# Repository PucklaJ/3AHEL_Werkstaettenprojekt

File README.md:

# 3AHEL_Werkstaettenprojekt
Hier findet man alle Dateien für unser Werktättenprojekt

Jahrgang: 2016/17
Personen:
	- Karayanov Vitaliy
	- Mujic Haris
	- Pucher Jonas

Arbeitszeit: 11x8 Schulstunden

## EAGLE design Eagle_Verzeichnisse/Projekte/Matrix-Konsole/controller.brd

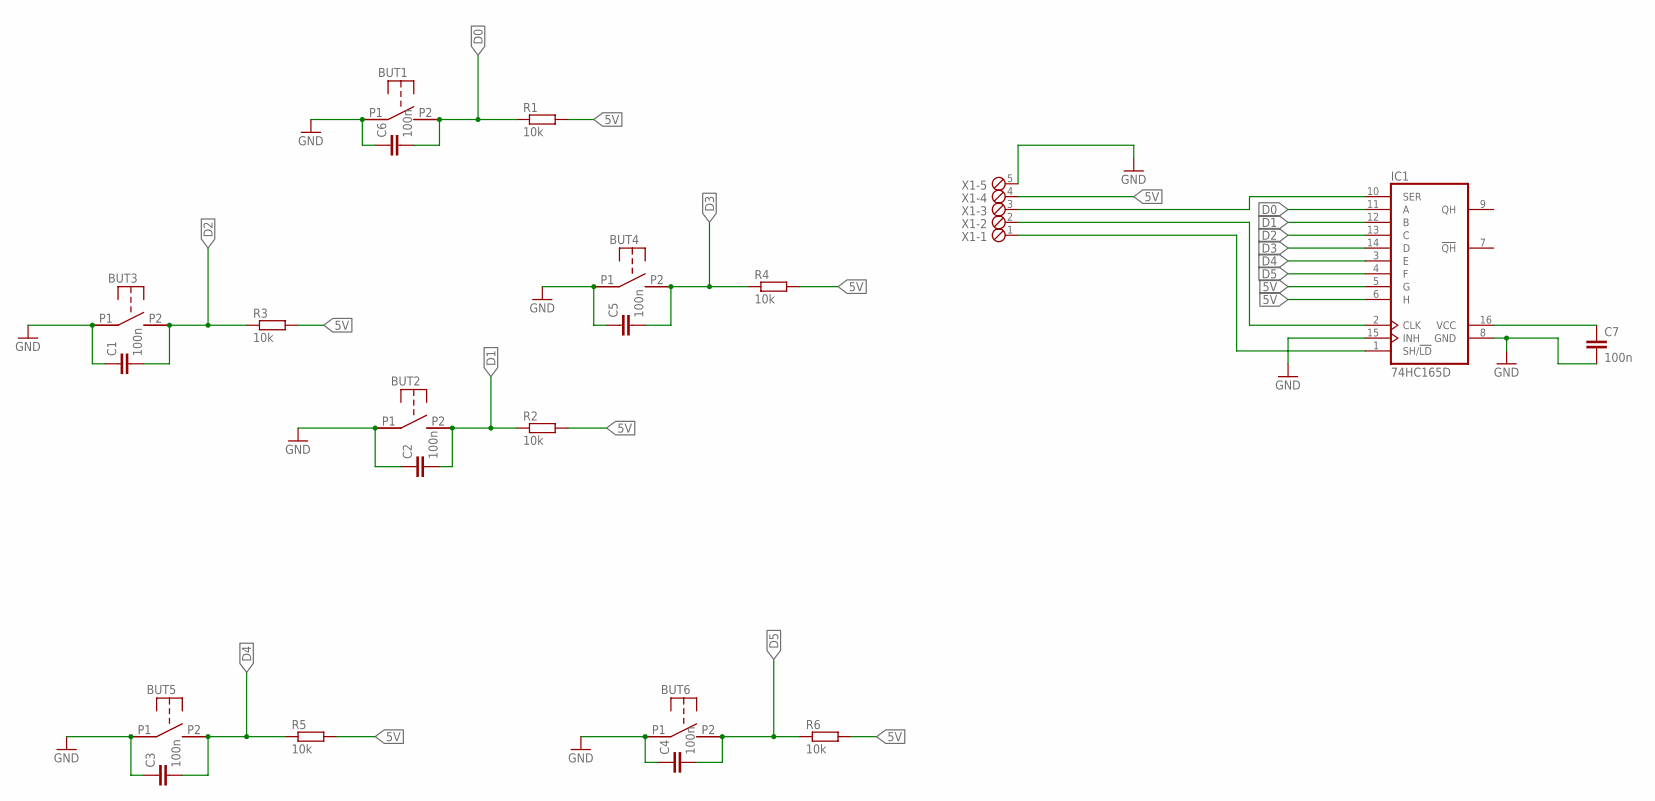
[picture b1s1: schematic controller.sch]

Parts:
BUT1, BUT2, BUT3, BUT4, BUT5, BUT6: BUTTON_DEV; BUTTON_PACK
C1, C2, C3, C4, C5, C6, C7: 100n; C0805
IC1: 74HC165D; SO16
R1, R2, R3, R4, R5, R6: 10k; M3516
X1: MPT5; 5POL254

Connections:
5V: C7.1, IC1.5 (G), IC1.6 (H), IC1.16 (VCC), R1.2, R2.2, R3.2, R4.2, R5.2, R6.2, X1.4
D0: BUT1.P2, BUT1.P2' (P2), C6.2, IC1.11 (A), R1.1
D1: BUT2.P2, BUT2.P2' (P2), C2.2, IC1.12 (B), R2.1
D2: BUT3.P2, BUT3.P2' (P2), C1.2, IC1.13 (C), R3.1
D3: BUT4.P2, BUT4.P2' (P2), C5.2, IC1.14 (D), R4.1
D4: BUT5.P2, BUT5.P2' (P2), C3.2, IC1.3 (E), R5.1
D5: BUT6.P2, BUT6.P2' (P2), C4.2, IC1.4 (F), R6.1
GND: BUT1.P1, BUT1.P1' (P1), BUT2.P1, BUT2.P1' (P1), BUT3.P1, BUT3.P1' (P1), BUT5.P1, BUT5.P1' (P1), BUT6.P1, BUT6.P1' (P1), C1.1, C2.1, C3.1, C4.1, C6.1, C7.2, IC1.8 (GND), IC1.15 (INH), X1.5
N3: BUT4.P1, BUT4.P1' (P1), C5.1
unnamed: IC1.1 (SH/!LD), X1.1
unnamed: IC1.2 (CLK), X1.2
unnamed: IC1.10 (SER), X1.3

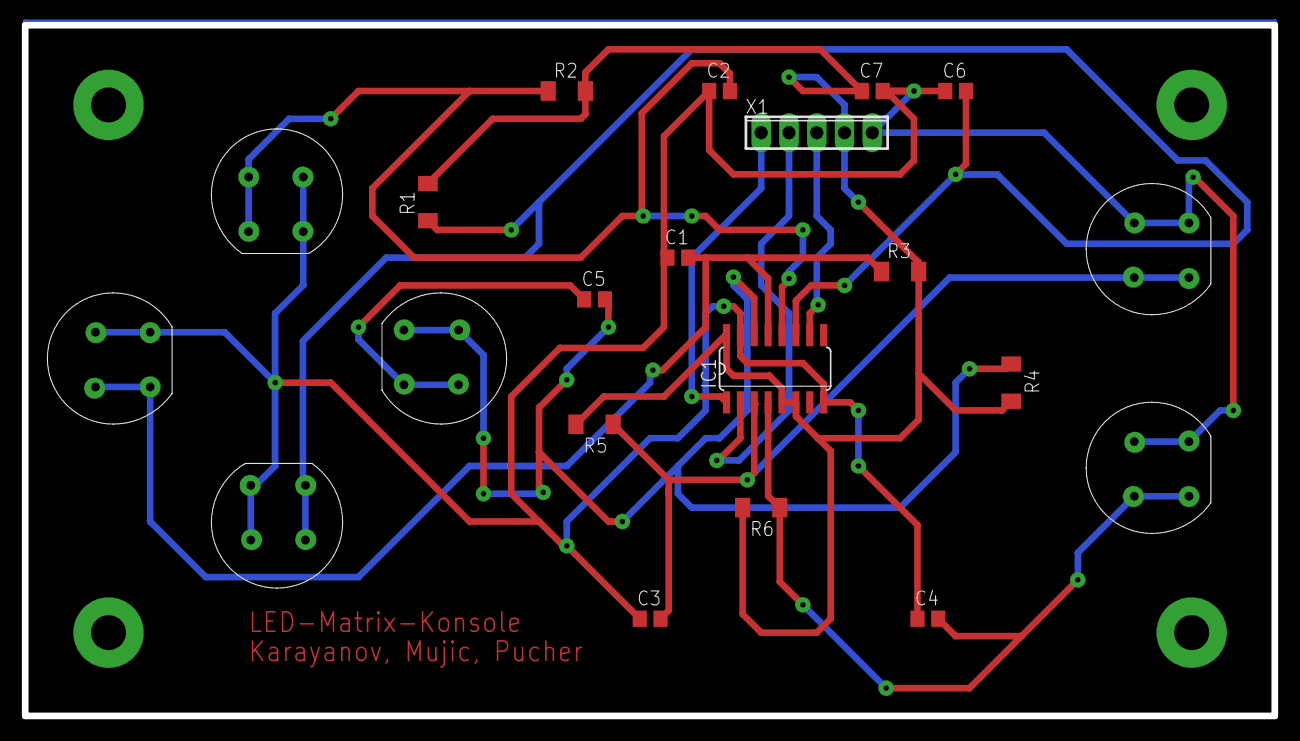
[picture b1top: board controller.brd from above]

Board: 2 copper layers, 114.3 x 63.2 mm, 21 parts (0 on the bottom side), 12 nets.

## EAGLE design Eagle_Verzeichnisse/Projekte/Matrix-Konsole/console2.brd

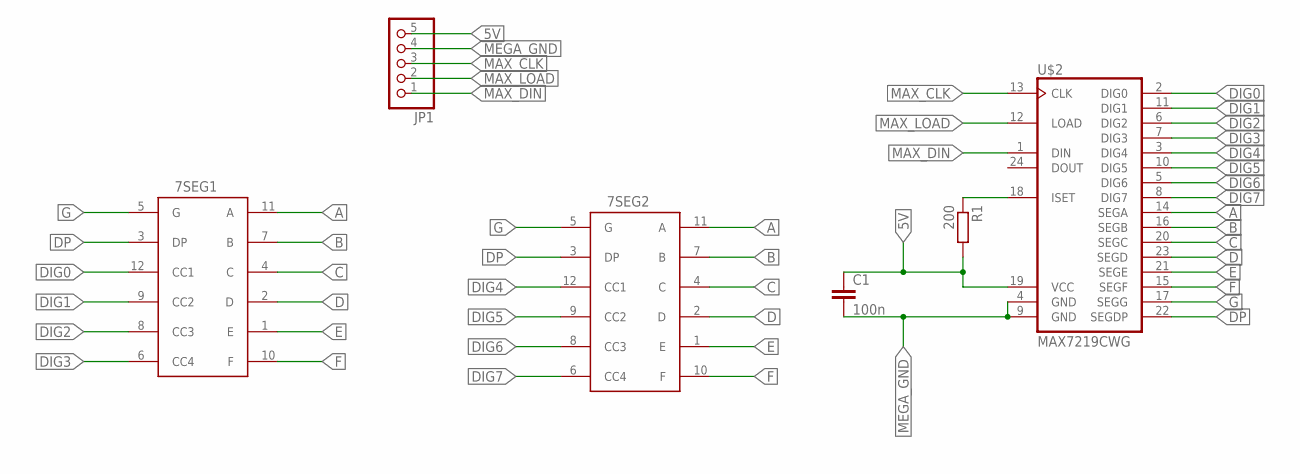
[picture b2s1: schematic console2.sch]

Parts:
7SEG1, 7SEG2: 7SEG_DEV; 7SEG_PACK
C1: 100n; C0805
JP1: PINHD-1X5; 1X05
R1: 200; M3516
U$2: MAX7219CWG; SO24L

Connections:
5V: C1.1, JP1.5, R1.2, U$2.19 (VCC)
A: 7SEG1.11 (A), 7SEG2.11 (A), U$2.14 (SEGA)
B: 7SEG1.7 (B), 7SEG2.7 (B), U$2.16 (SEGB)
C: 7SEG1.4 (C), 7SEG2.4 (C), U$2.20 (SEGC)
D: 7SEG1.2 (D), 7SEG2.2 (D), U$2.23 (SEGD)
DIG0: 7SEG1.12 (CC1), U$2.2 (DIG0)
DIG1: 7SEG1.9 (CC2), U$2.11 (DIG1)
DIG2: 7SEG1.8 (CC3), U$2.6 (DIG2)
DIG3: 7SEG1.6 (CC4), U$2.7 (DIG3)
DIG4: 7SEG2.12 (CC1), U$2.3 (DIG4)
DIG5: 7SEG2.9 (CC2), U$2.10 (DIG5)
DIG6: 7SEG2.8 (CC3), U$2.5 (DIG6)
DIG7: 7SEG2.6 (CC4), U$2.8 (DIG7)
DP: 7SEG1.3 (DP), 7SEG2.3 (DP), U$2.22 (SEGDP)
E: 7SEG1.1 (E), 7SEG2.1 (E), U$2.21 (SEGE)
F: 7SEG1.10 (F), 7SEG2.10 (F), U$2.15 (SEGF)
G: 7SEG1.5 (G), 7SEG2.5 (G), U$2.17 (SEGG)
MAX_CLK: JP1.3, U$2.13 (CLK)
MAX_DIN: JP1.1, U$2.1 (DIN)
MAX_ISET: R1.1, U$2.18 (ISET)
MAX_LOAD: JP1.2, U$2.12 (LOAD)
MEGA_GND: C1.2, JP1.4, U$2.4 (GND), U$2.9 (GND)

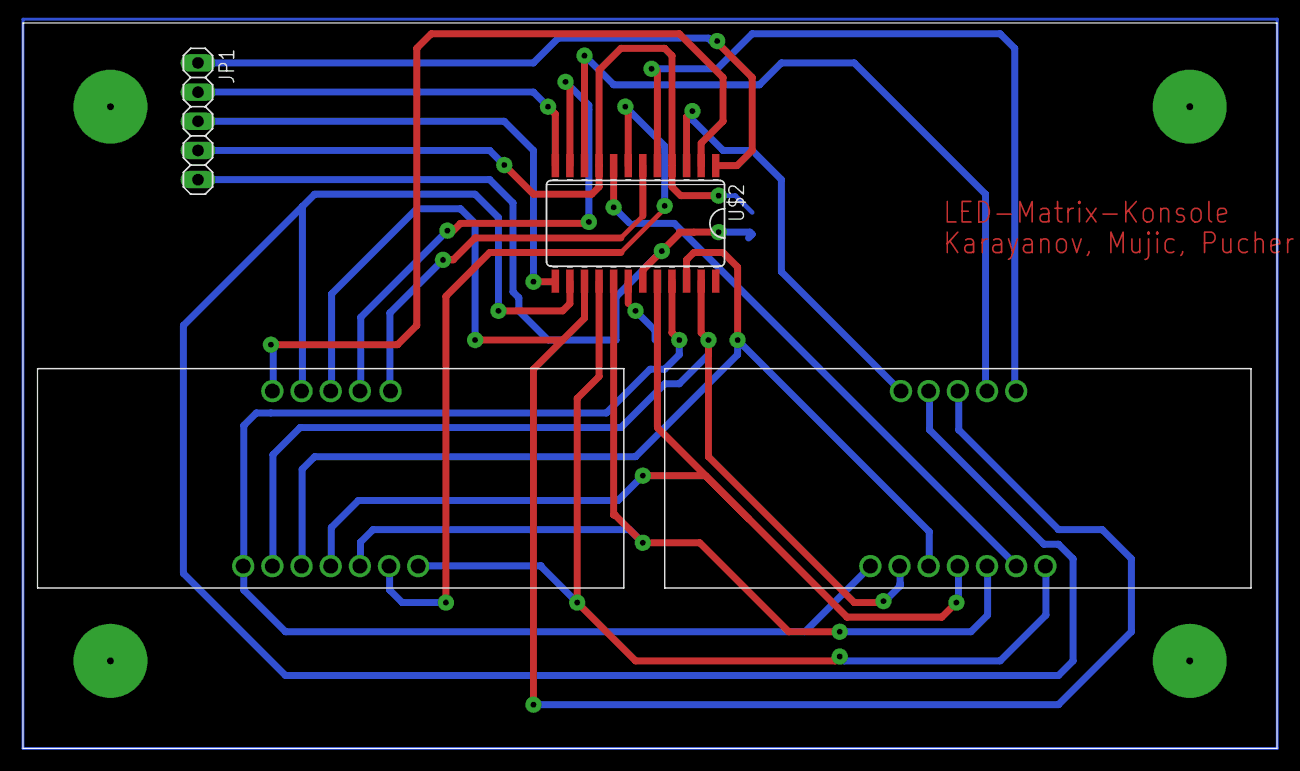
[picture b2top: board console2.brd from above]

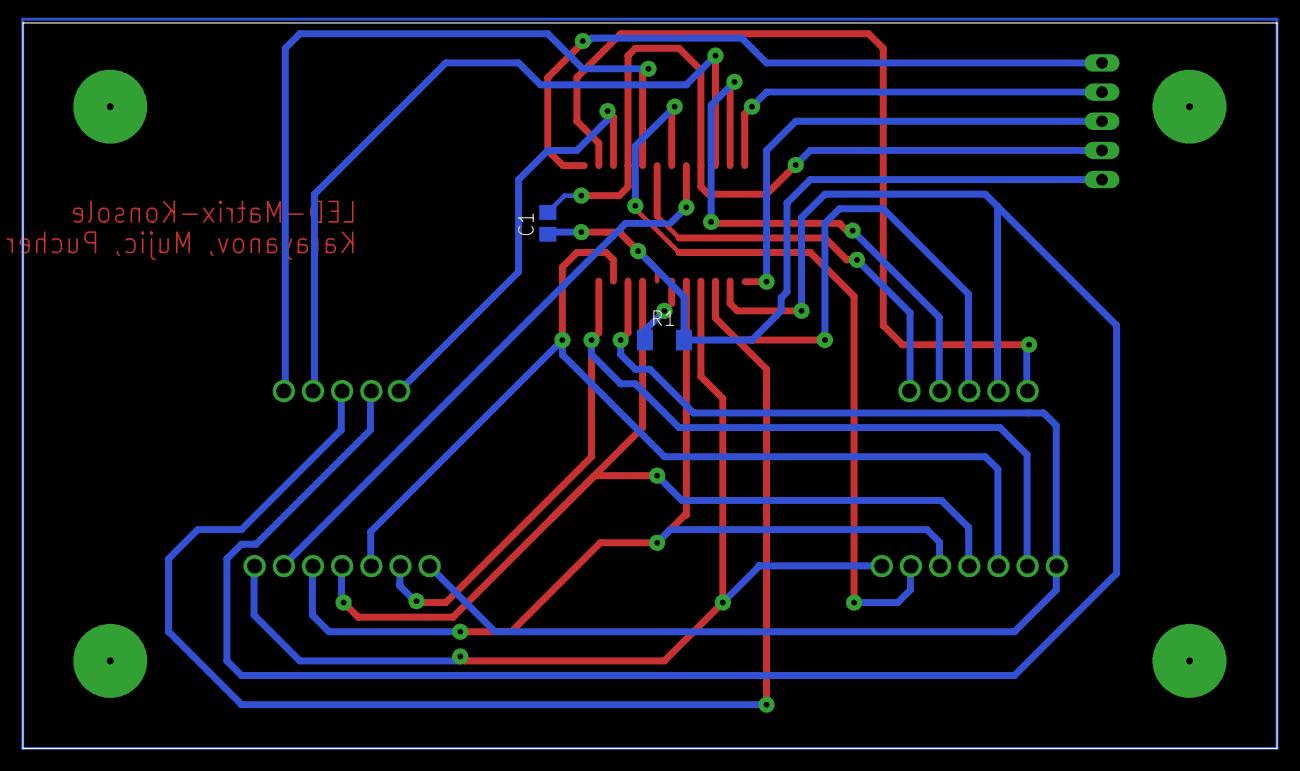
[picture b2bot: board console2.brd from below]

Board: 2 copper layers, 109.2 x 63.2 mm, 6 parts (2 on the bottom side), 22 nets.

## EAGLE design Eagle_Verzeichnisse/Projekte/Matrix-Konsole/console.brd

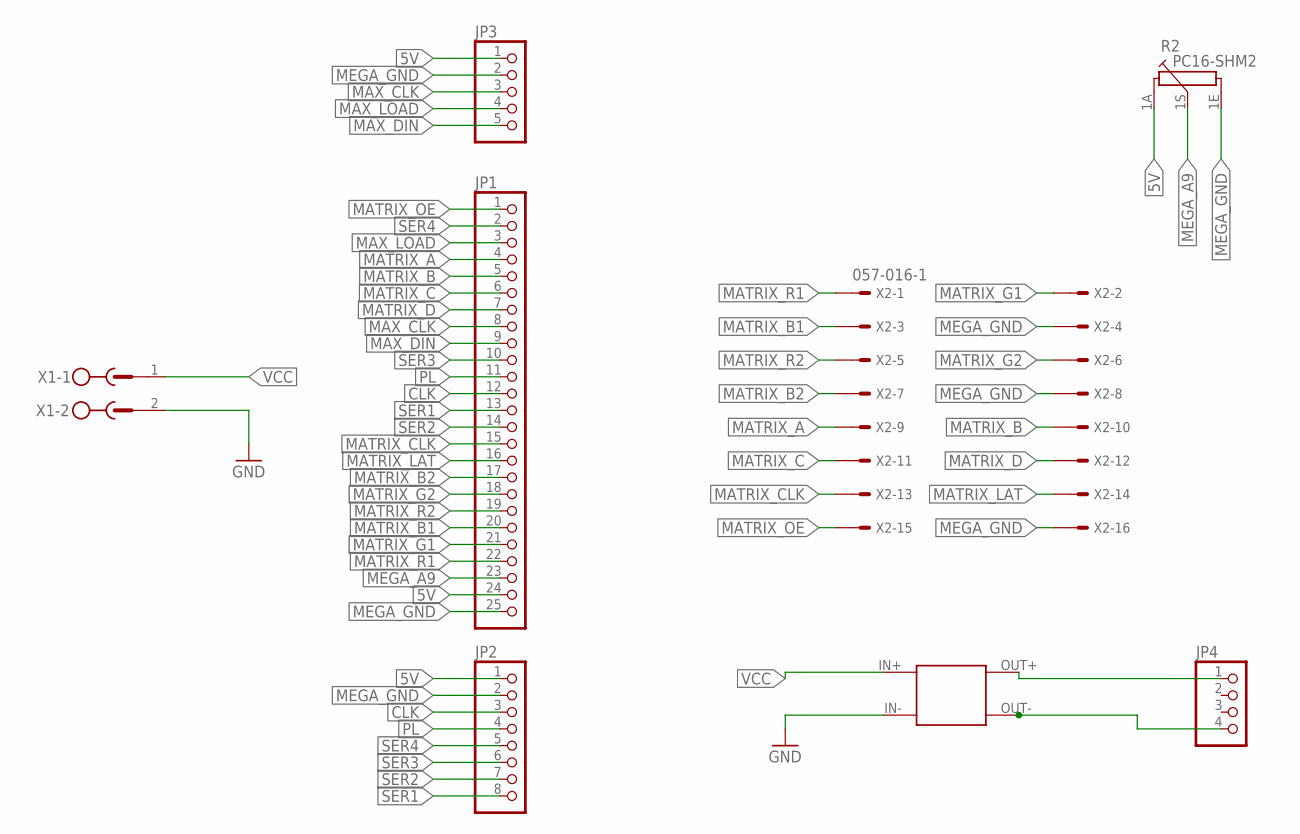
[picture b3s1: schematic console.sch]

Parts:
JP1: PINHD-1X25; 1X25
JP2: PINHD-1X8; 1X08
JP3: PINHD-1X5; 1X05
JP4: PINHD-1X4; 1X04
R2: PC16-SHM2
U$1: SPGRGL_DEV; SPGRGL_PACK
X1: MSTBV2
X2: 057-016-1

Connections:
5V: JP1.24, JP2.1, JP3.1, R2.1A
CLK: JP1.12, JP2.3
GND: U$1.IN-, X1.2
MATRIX_A: JP1.4, X2.9
MATRIX_B: JP1.5, X2.10
MATRIX_B1: JP1.20, X2.3
MATRIX_B2: JP1.17, X2.7
MATRIX_C: JP1.6, X2.11
MATRIX_CLK: JP1.15, X2.13
MATRIX_D: JP1.7, X2.12
MATRIX_G1: JP1.21, X2.2
MATRIX_G2: JP1.18, X2.6
MATRIX_GND: JP4.4, U$1.OUT-
MATRIX_LAT: JP1.16, X2.14
MATRIX_OE: JP1.1, X2.15
MATRIX_R1: JP1.22, X2.1
MATRIX_R2: JP1.19, X2.5
MATRIX_VCC: JP4.1, U$1.OUT+
MAX_CLK: JP1.8, JP3.3
MAX_DIN: JP1.9, JP3.5
MAX_LOAD: JP1.3, JP3.4
MEGA_A9: JP1.23, R2.1S
MEGA_GND: JP1.25, JP2.2, JP3.2, R2.1E, X2.4, X2.8, X2.16
PL: JP1.11, JP2.4
SER1: JP1.13, JP2.8
SER2: JP1.14, JP2.7
SER3: JP1.10, JP2.6
SER4: JP1.2, JP2.5
VCC: U$1.IN+, X1.1

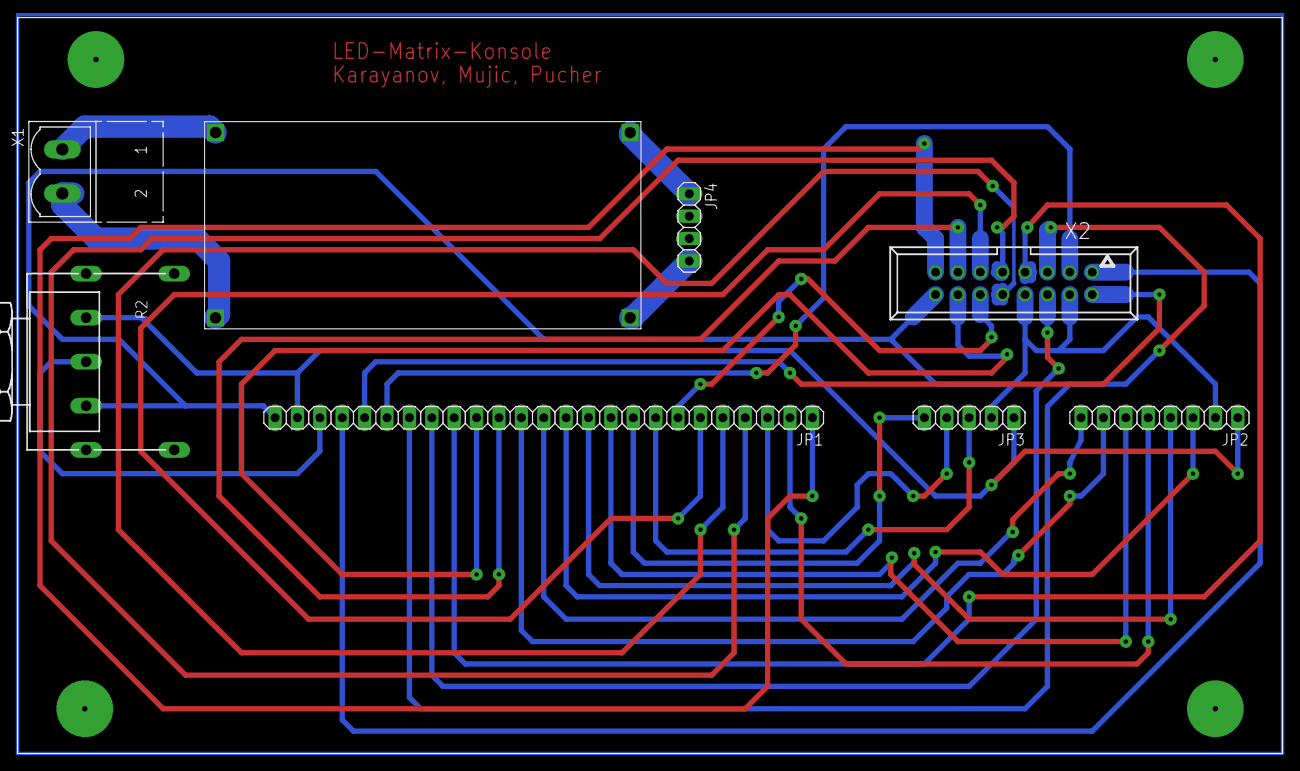
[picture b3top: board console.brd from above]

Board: 2 copper layers, 143.5 x 83.5 mm, 8 parts (0 on the bottom side), 29 nets.

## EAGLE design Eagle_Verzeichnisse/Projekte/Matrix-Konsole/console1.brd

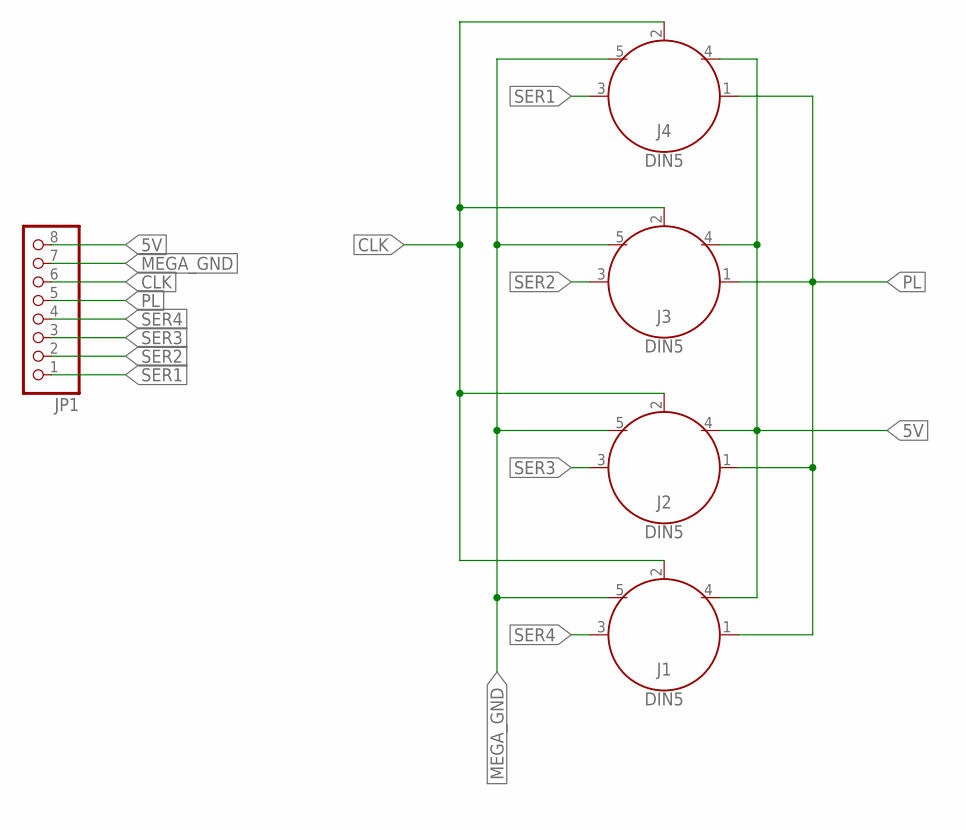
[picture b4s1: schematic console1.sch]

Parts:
J1, J2, J3, J4: DIN5; DIN5-RA-PTH
JP1: PINHD-1X8; 1X08

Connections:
5V: J1.4, J2.4, J3.4, J4.4, JP1.8
CLK: J1.2, J2.2, J3.2, J4.2, JP1.6
MEGA_GND: J1.5, J2.5, J3.5, J4.5, JP1.7
PL: J1.1, J2.1, J3.1, J4.1, JP1.5
SER1: J4.3, JP1.1
SER2: J3.3, JP1.2
SER3: J2.3, JP1.3
SER4: J1.3, JP1.4

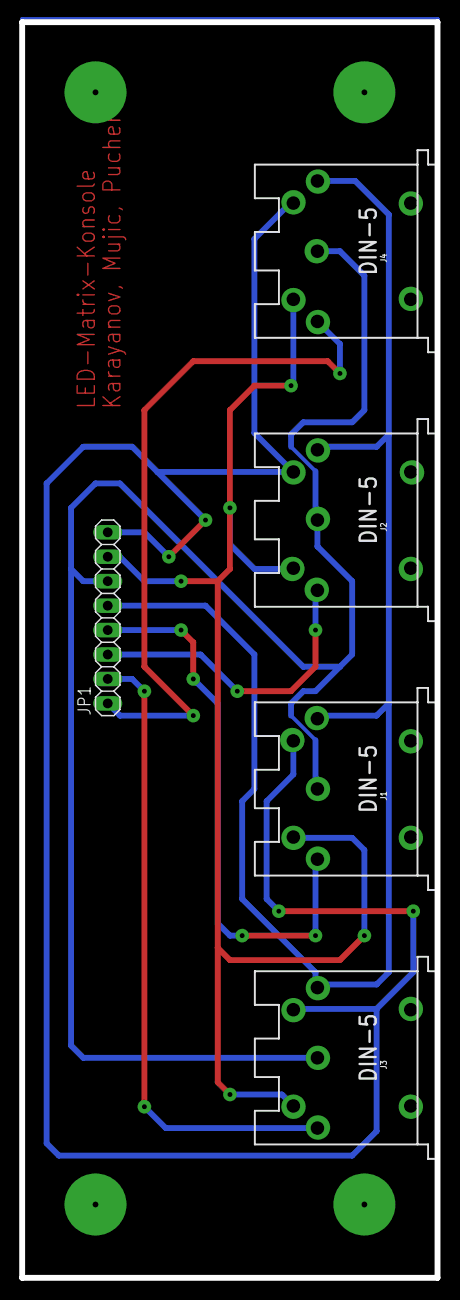
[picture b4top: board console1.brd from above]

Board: 2 copper layers, 43.2 x 130.5 mm, 5 parts (0 on the bottom side), 8 nets.

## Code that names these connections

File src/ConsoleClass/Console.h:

#ifndef CONSOLE_H
#define CONSOLE_H
#include <RGBmatrixPanel.h>
#include <LedControl.h>
#include "Controller.h"

#define MATRIX_A A0
#define MATRIX_B A1
#define MATRIX_C A2
#define MATRIX_D A3
#define MATRIX_SCLK 11
#define MATRIX_LAT 10
#define MATRIX_OE 9

#define MAX_DATA 23
#define MAX_CLK 32
#define MAX_CS 31

#define BRIGHT_POTI A4

#define CON_SER1 35
#define CON_SER2 36
#define CON_SER3 22
#define CON_SER4 30
#define CON_CLK 34
#define CON_PL 33

#define WHITE 255,255,255
#define BLACK 0,0,0
#define RED 255,0,0
#define GREEN 0,255,0
#define BLUE 0,0,255
#define YELLOW 255,255,0
#define PINK_COLOR 255,20,147
#define BROWN 139,69,19

#ifndef NUM_GAMES
  #define NUM_GAMES 1
#endif

#define MENU_STATE 0
#define PLAY_STATE 1

class Game;

struct Vec2
{
  int x;
  int y;
};

struct ColorRGB
{
  uint8_t r;
  uint8_t g;
  uint8_t b;

  ColorRGB(uint8_t _r,uint8_t _g,uint8_t _b)
  {
    r = _r;
    g = _g;
    b = _b;
  }
  ColorRGB()
  {
    r = 0;
    g = 0;
    b = 0;
  }
};

class Console : public RGBmatrixPanel
{
	public:
		Console();
		~Console();


  	void init();
  	void update();
  	void render();
  	void quit();
  
    void setScoreString(byte,const char*);
    void setScoreNumber(byte,unsigned int);

    float getBrightness() const;

    uint16_t Color(float,float,float);
    uint16_t Color(const ColorRGB&);

    const Controller& getController(byte c) const {return m_controllers[c];}
    LedControl* getMAX() {return m_ledControl;}

    void setGame(byte,Game*);

  private:
    void initMAX();
    void initPins();
    void testStartup();
    void readBrightness();
    void readInput();
    void switchState(byte);

    void menuControl();
    void playControl();
    void updateGames();
    void renderGames();
  
    LedControl* m_ledControl = nullptr;
    float m_brightness = 1.0f;
    Controller m_controllers[4];
    Game* m_games[NUM_GAMES];
    long m_curGame = 0;
    byte m_curState = MENU_STATE;
};


#endif

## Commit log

2017-03-03 Added Arbeitsnachweis Ordner
2017-03-03 Added Schaltplan Ordner
2017-03-10 Added a few files
2017-03-10 Changed Readme
2017-03-10 Added a new Arbeitsnachweis and documentation
2017-03-10 Added Stückliste
2017-03-11 Added a few parts to circuit diagram
2017-03-11 Added circuit diagrams, Changed Stückliste
2017-03-11 Changed 79HC to 74HC in Stückliste
2017-03-12 Removed USB, Changed Labels
2017-03-13 Added youtube.txt
2017-03-13 Removed Bauer,Auer,Kerschner from Readme
2017-03-17 Added MAX7219 Library
2017-03-17 Added Source Code
2017-03-17 Added MAX7219, Added Potentiometer, Made curcuit diagram clearer, Changed Connectors
2017-03-17 Added Board to console, Added Pin header
2017-03-19 Added Z-Diode
2017-03-19 Changed z-Diode-resistor to 10 Ohm
2017-03-22 Changed the matrix board
2017-03-24 Added Spannungsregler
2017-03-24 Added Layout for console
2017-03-31 Added Bestellnumnmern to Stückliste, Added Bohrungen to console-layout
2017-03-31 Added controller-layout, Improved console-layout
2017-03-31 Improved layouts
2017-04-06 Splitted the console-layout into three boards and improved the layouts
2017-04-07 Made final changes to the layout and added PDF-Files
2017-05-01 Added SourceCode: Console Class, Controller Class, Game Class and one Game: TankGame
2017-05-03 Added Löt-constructions
2017-05-03 Added input to TankGame
2017-05-03 Added Menu to TankGame
2017-05-17 Added Package_sketch
2017-06-07 Added pictures and srote most of the documentation
2017-06-07 Finished Tank Game
2017-06-07 Removed playControl
2017-06-08 Just Merging
2017-06-08 Added test for controller
2017-06-08 Added Präsentation
2017-06-08 Added text to the presentation
2017-06-08 Completed presentation
2017-06-08 Added pictures to the documentation
2017-06-08 almost finished documentation
2017-08-28 Strange

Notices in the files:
parts and their libraries:
SparkFun-Connectors: Licensing: Creative Commons ShareAlike 4.0 International - https://creativecommons.org/licenses/by-sa/4.0
